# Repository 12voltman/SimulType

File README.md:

# SimulType
A collection of keyboard layouts and designs that emphasize data input through two handed use of the number pad with a keyboard or arrow keys

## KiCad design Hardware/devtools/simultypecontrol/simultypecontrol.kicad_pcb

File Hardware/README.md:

# Simultype Hardware
Described below are the different categories of PCBs and 3D files used for the creation of a SimulType keyboard.  By design, each Simultype keyboard is made up of at least 2 PCBs:  
- Key Matrix: comes in the various size standards, and contains the switches, LEDS, and some supporting ICs
- Controller Board: has the main processor, and any external connectors or peripherals (USB, battery, OLEDs, encoders, etc.)
- Space Sensor Board: flex-PCB to fit inside space bar and allow capacitive touch interaction (optional)

## Dev Tools
Currently I have a basic control board for testing that simply lets you use a Pro Micro to evaluate functionality.  Due to pin count limitations, this requires using shift registers for the column lines.  This basic control board was designed with the nice! Nano in mind (or 3rd party equivalent) and supports the extra pins needed for a battery connection.  
<br>
Additionally there is a programming tool designed to use pogo pins to mate with test points on a key matrix for testing/programming of the ICs on board such as the LED driver, identification EEPROM, and capacitive touch sensor.  This board is designed to be hand-soldered and mainly used in series production, as all its communications are carried out over I2C which is available to the standard controller.  

## Creating a controller board
Key requirements for a controller to work across the widest range of Simultype key matrixes:  
- I<sup>2</sup>C (ideally high speed) needed for secondary features and LED drivers if used
- 3.3V regulated supply (low power, needed for minor peripherals)
- Higher voltage, high-current supply (needed for LEDS, may be 5V from USB or direct battery voltage of 4.2V or whatever)
- 4 GPIO for supporting low-power mode, interrupt, and addressable LEDs
- Matrix driving
  - 24 Column drivers, ideally with moderate power sourcing support for driving hall sensors on analog boards
  - 8 Row receive lines, ideally with ADC function for analog boards
  - (Optional) To drastically reduce pin counts required, column drivers can be Serial-In Parallel-Out (SIPO) shift registers, as implemented on dev controller board

## FPC Pinout
The FPC cable linking the key matrix and the controller is designed to be standard across all variants, and if anyone else wants to use it more power to you.  Here is the pinout from 1 (leftmost) to 45 (rightmost) both when viewed from above when the keyboard is assembled.  
| Pin | Name      | Function                                                                                       |
|-----|-----------|------------------------------------------------------------------------------------------------|
| 1   | COL24     | Leftmost column drive                                                                          |
| 2   | COL23     |                                                                                                |
| 3   | COL22     |                                                                                                |
| 4   | COL21     |                                                                                                |
| 5   | COL20     |                                                                                                |
| 6   | COL19     |                                                                                                |
| 7   | COL18     |                                                                                                |
| 8   | COL17     |                                                                                                |
| 9   | COL16     |                                                                                                |
| 10  | COL15     |                                                                                                |
| 11  | COL14     |                                                                                                |
| 12  | COL13     |                                                                                                |
| 13  | COL12     |                                                                                                |
| 14  | COL11     |                                                                                                |
| 15  | COL10     |                                                                                                |
| 16  | COL9      |                                                                                                |
| 17  | ROW8      | Bottommost row receive (connect to analog input on controller if possible for analog matrix)   |
| 18  | ROW7      |                                                                                                |
| 19  | ROW6      |                                                                                                |
| 20  | ROW5      |                                                                                                |
| 21  | ROW4      |                                                                                                |
| 22  | ROW3      |                                                                                                |
| 23  | ROW2      |                                                                                                |
| 24  | ROW1      | Topmost row receive (connect to analog input on controller if possible for analog matrix)      |
| 25  | GND       |                                                                                                |
| 26  | GND       |                                                                                                |
| 27  | GND       |                                                                                                |
| 28  | 3.3V      | Supply for non-LED ICs                                                                         |
| 29  | 5V        |                                                                                                |
| 30  | 5V        | Supply for LEDS (allowed to vary, must be high power)                                          |
| 31  | 5V        |                                                                                                |
| 32  | APACLK    | Clock for APA and other clock+data LEDS (may not be used on all boards)                        |
| 33  | APANEODAT | Data for Neopixel/APA LEDs (may not be used on all boards)                                     |
| 34  | SDA       | I2C data line                                                                                  |
| 35  | SCL       | I2C clock line                                                                                 |
| 36  | INT       | Shared interrupt line, active low                                                              |
| 37  | LEDOFF    | Hard shutoff for LEDs (may be used by either LED driver, or power gating for addressable LEDs) |
| 38  | COL8      |                                                                                                |
| 39  | COL7      |                                                                                                |
| 40  | COL6      |                                                                                                |
| 41  | COL5      |                                                                                                |
| 42  | COL4      |                                                                                                |
| 43  | COL3      |                                                                                                |
| 44  | COL2      |                                                                                                |
| 45  | COL1      | Rightmost column drive                                                                         |

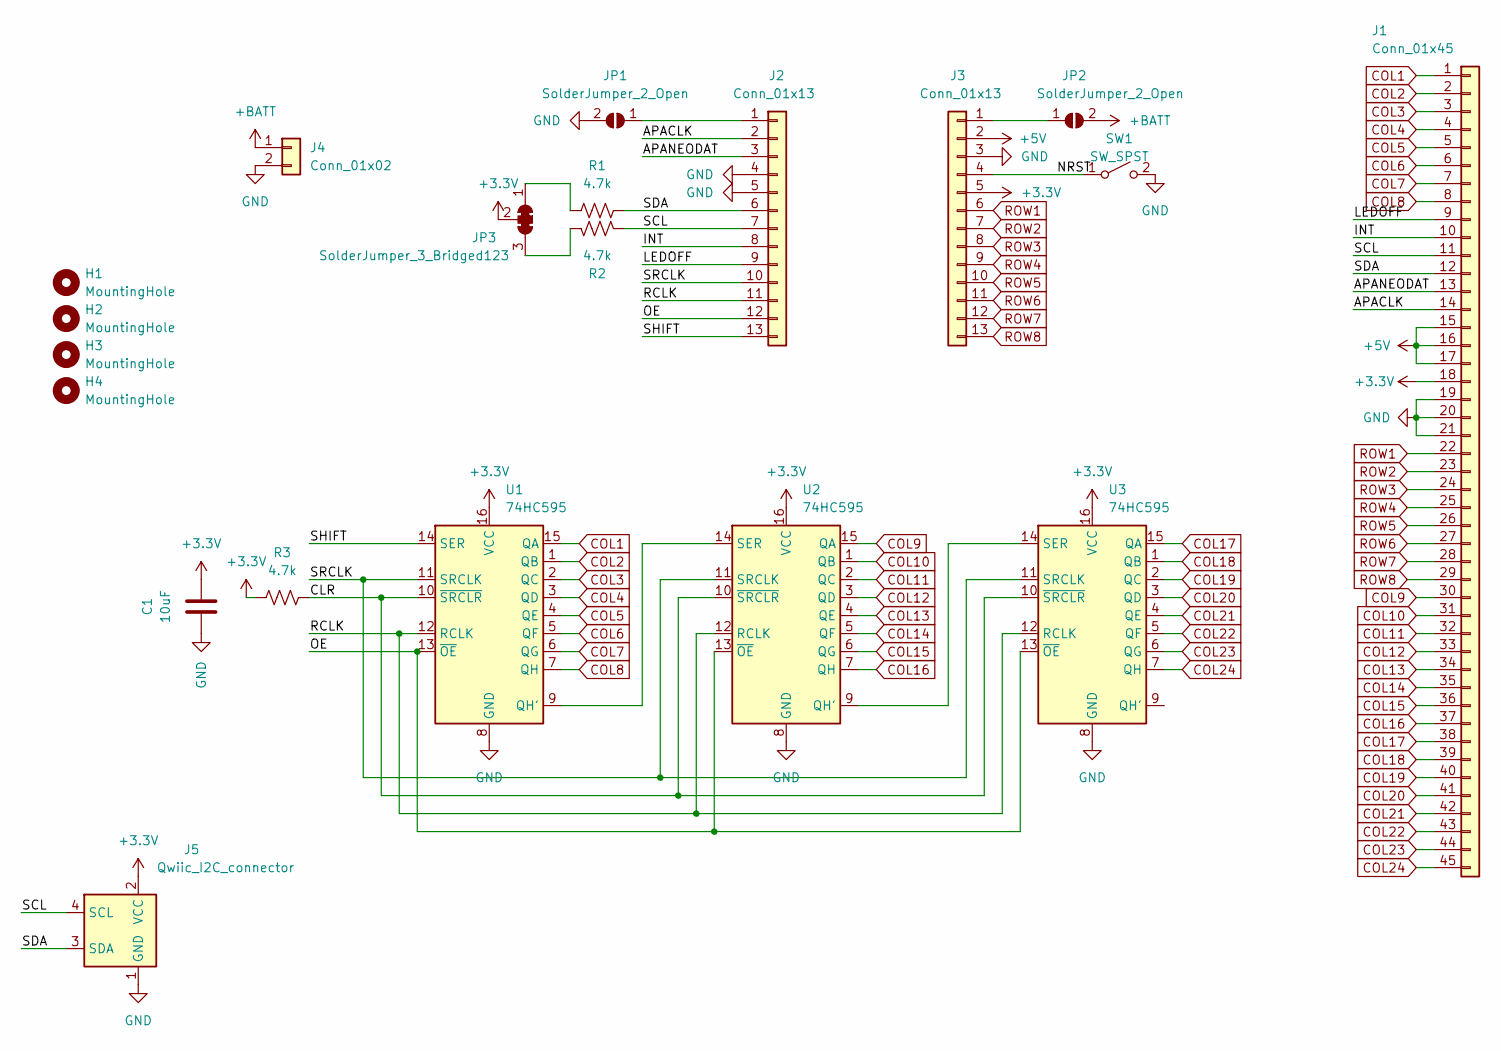
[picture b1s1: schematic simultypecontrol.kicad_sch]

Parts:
C1: 10uF; C_0805_2012Metric; LCSC C1713
H1, H2, H3, H4: MountingHole; breakoffm3hole
J1: Conn_01x45; TE_4-1734839-5_1x45-1MP_P0.5mm_Horizontal; LCSC C2998867
J2, J3: Conn_01x13; PinHeader_1x13_P2.54mm_Vertical; LCSC C2986992
J4: Conn_01x02; JST_PH_S2B-PH-K_1x02_P2.00mm_Horizontal; LCSC C49992
J5: Qwiic_I2C_connector; JST_SH_SM04B-SRSS-TB_1x04-1MP_P1.00mm_Horizontal; LCSC C7433425
JP1, JP2: SolderJumper_2_Open; SolderJumper-2_P1.3mm_Open_TrianglePad1.0x1.5mm
JP3: SolderJumper_3_Bridged123; SolderJumper-3_P1.3mm_Bridged123_RoundedPad1.0x1.5mm
R1, R2, R3: 4.7k; R_0603_1608Metric; LCSC C25999
SW1: SW_SPST; SW_PUSH_6mm; LCSC C5340136
U1, U2, U3: 74HC595; DHVQFN-16-1EP_2.5x3.5mm_P0.5mm_EP1x2mm; LCSC C730243

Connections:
+3.3V: C1.1, J1.18, J3.5, J5.2 (VCC), JP3.2 (C), R3.1, U1.16 (VCC), U2.16 (VCC), U3.16 (VCC)
+5V: J1.15, J1.16, J1.17, J3.2
+BATT: J4.1, JP2.2 (B)
/APACLK: J1.14, J2.2
/APANEODAT: J1.13, J2.3
/CLR: R3.2, U1.10 (~SRCLR), U2.10 (~SRCLR), U3.10 (~SRCLR)
/INT: J1.10, J2.8
/LEDOFF: J1.9, J2.9
/NRST: J3.4, SW1.1 (A)
/OE: J2.12, U1.13 (~OE), U2.13 (~OE), U3.13 (~OE)
/RCLK: J2.11, U1.12 (RCLK), U2.12 (RCLK), U3.12 (RCLK)
/SCL: J1.11, J2.7, J5.4 (SCL), R2.2
/SDA: J1.12, J2.6, J5.3 (SDA), R1.2
/SHIFT: J2.13, U1.14 (SER)
/SRCLK: J2.10, U1.11 (SRCLK), U2.11 (SRCLK), U3.11 (SRCLK)
COL1: J1.1, U1.15 (QA)
COL2: J1.2, U1.1 (QB)
COL3: J1.3, U1.2 (QC)
COL4: J1.4, U1.3 (QD)
COL5: J1.5, U1.4 (QE)
COL6: J1.6, U1.5 (QF)
COL7: J1.7, U1.6 (QG)
COL8: J1.8, U1.7 (QH)
COL9: J1.30, U2.15 (QA)
COL10: J1.31, U2.1 (QB)
COL11: J1.32, U2.2 (QC)
COL12: J1.33, U2.3 (QD)
COL13: J1.34, U2.4 (QE)
COL14: J1.35, U2.5 (QF)
COL15: J1.36, U2.6 (QG)
COL16: J1.37, U2.7 (QH)
COL17: J1.38, U3.15 (QA)
COL18: J1.39, U3.1 (QB)
COL19: J1.40, U3.2 (QC)
COL20: J1.41, U3.3 (QD)
COL21: J1.42, U3.4 (QE)
COL22: J1.43, U3.5 (QF)
COL23: J1.44, U3.6 (QG)
COL24: J1.45, U3.7 (QH)
GND: C1.2, J1.19, J1.20, J1.21, J2.4, J2.5, J3.3, J4.2, J5.1 (GND), J5.MP (VSS), JP1.2 (B), SW1.2 (B), U1.8 (GND), U2.8 (GND), U3.8 (GND)
unnamed: J2.1, JP1.1 (A)
unnamed: J3.1, JP2.1 (A)
unnamed: JP3.1 (A), R1.1
unnamed: JP3.3 (B), R2.1
unnamed: U1.9 (QH'), U2.14 (SER)
unnamed: U2.9 (QH'), U3.14 (SER)
ROW1: J1.22, J3.6
ROW2: J1.23, J3.7
ROW3: J1.24, J3.8
ROW4: J1.25, J3.9
ROW5: J1.26, J3.10
ROW6: J1.27, J3.11
ROW7: J1.28, J3.12
ROW8: J1.29, J3.13

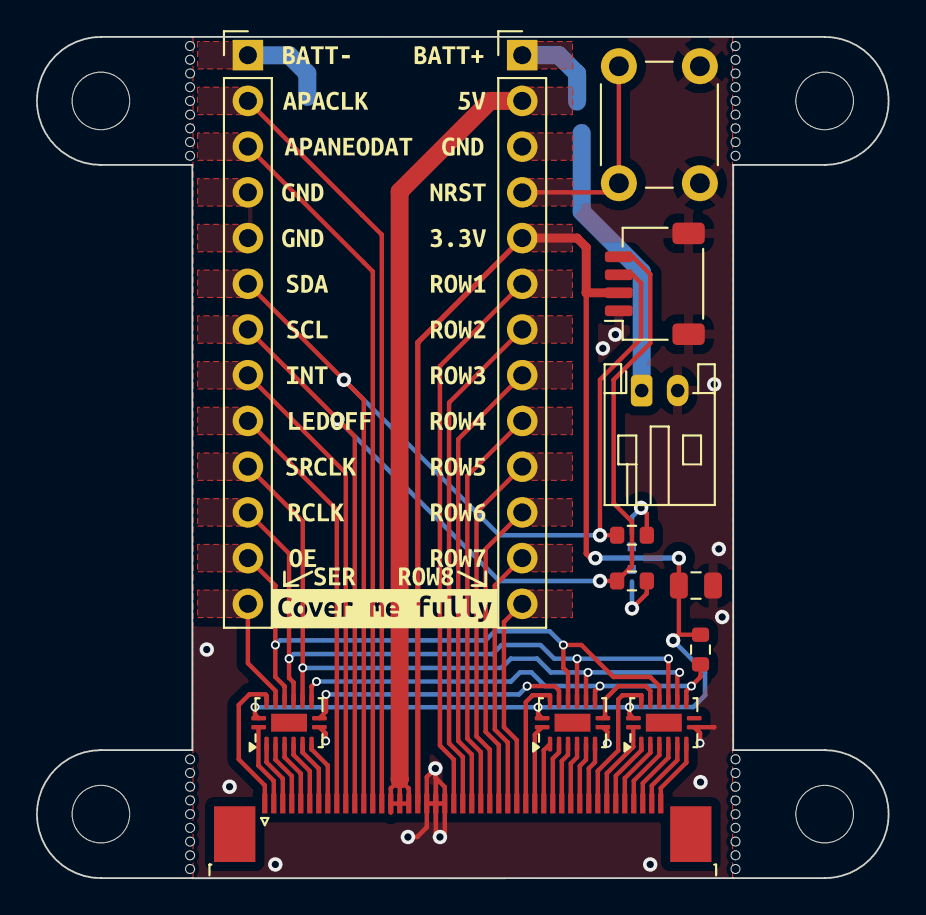
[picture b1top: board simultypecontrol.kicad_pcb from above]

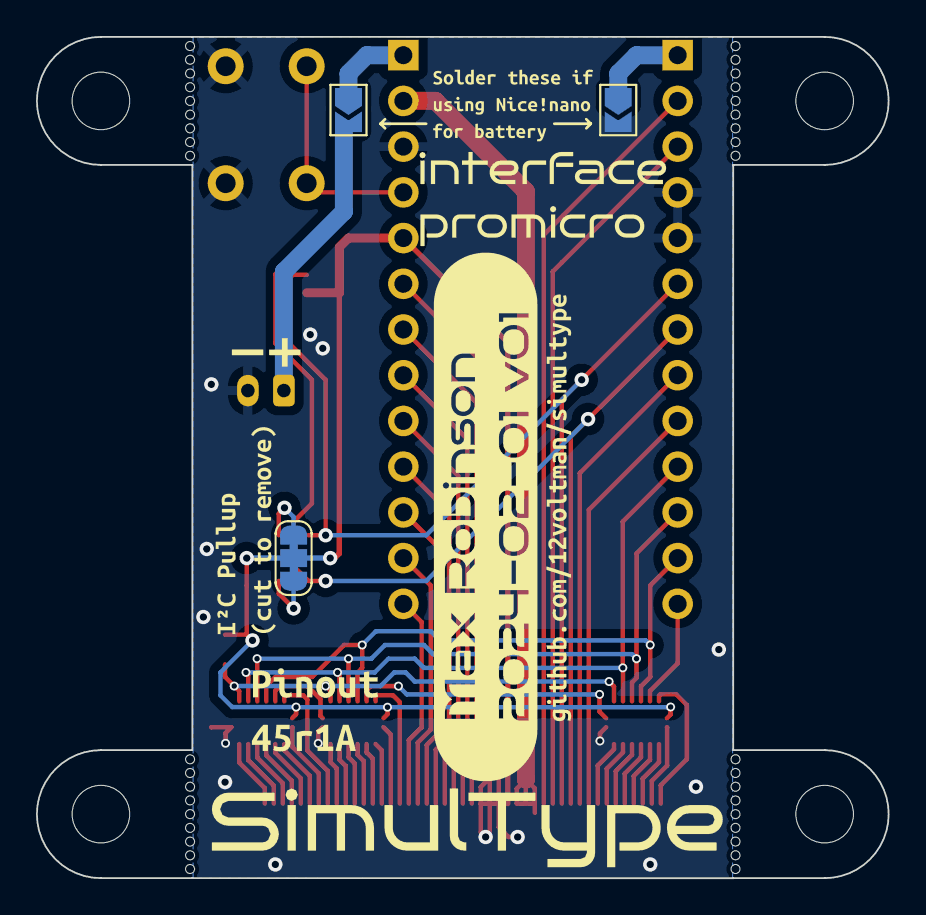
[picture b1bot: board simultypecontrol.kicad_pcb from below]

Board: 2 copper layers, 47.3 x 46.7 mm, 55 parts (11 on the bottom side), 54 nets.

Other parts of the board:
kibuzzard-65BDD6E5: G***; kibuzzard-65BDD6E5
kibuzzard-65BDD7EC: G***; kibuzzard-65BDD7EC
kibuzzard-65BDD62B: G***; kibuzzard-65BDD62B
kibuzzard-65BDD75E: G***; kibuzzard-65BDD75E
kibuzzard-65BDD614: G***; kibuzzard-65BDD614
kibuzzard-65BDD880: G***; kibuzzard-65BDD880
kibuzzard-65BE09D0: G***; kibuzzard-65BE09D0
kibuzzard-65BE0934: G***; kibuzzard-65BE0934
kibuzzard-65BEF9A5: G***; kibuzzard-65BEF9A5
kibuzzard-65BEF9C3: G***; kibuzzard-65BEF9C3
kibuzzard-65BEF9CF: G***; kibuzzard-65BEF9CF
kibuzzard-65BEF9D6: G***; kibuzzard-65BEF9D6
kibuzzard-65BEF9DC: G***; kibuzzard-65BEF9DC
kibuzzard-65BEF9E1: G***; kibuzzard-65BEF9E1
kibuzzard-65BEF9E8: G***; kibuzzard-65BEF9E8
kibuzzard-65BEF9F0: G***; kibuzzard-65BEF9F0
kibuzzard-65BEF9FD: G***; kibuzzard-65BEF9FD
kibuzzard-65BEF941: G***; kibuzzard-65BEF941
kibuzzard-65BEFA0F: G***; kibuzzard-65BEFA0F
kibuzzard-65BEFA1D: G***; kibuzzard-65BEFA1D
kibuzzard-65BEFA03: G***; kibuzzard-65BEFA03
kibuzzard-65BEFA3D: G***; kibuzzard-65BEFA3D
kibuzzard-65BEFA6D: G***; kibuzzard-65BEFA6D
kibuzzard-65BEFA08: G***; kibuzzard-65BEFA08
kibuzzard-65BEFA17: G***; kibuzzard-65BEFA17
kibuzzard-65BEFA24: G***; kibuzzard-65BEFA24
kibuzzard-65BEFA30: G***; kibuzzard-65BEFA30
kibuzzard-65BEFA36: G***; kibuzzard-65BEFA36
kibuzzard-65BEFA42: G***; kibuzzard-65BEFA42
kibuzzard-65BEFA48: G***; kibuzzard-65BEFA48
kibuzzard-65BEFA57: G***; kibuzzard-65BEFA57
kibuzzard-65BEFA60: G***; kibuzzard-65BEFA60
kibuzzard-65BEFA66: G***; kibuzzard-65BEFA66
kibuzzard-65C29BCC: G***; kibuzzard-65C29BCC
kibuzzard-65C25006: G***; kibuzzard-65C25006

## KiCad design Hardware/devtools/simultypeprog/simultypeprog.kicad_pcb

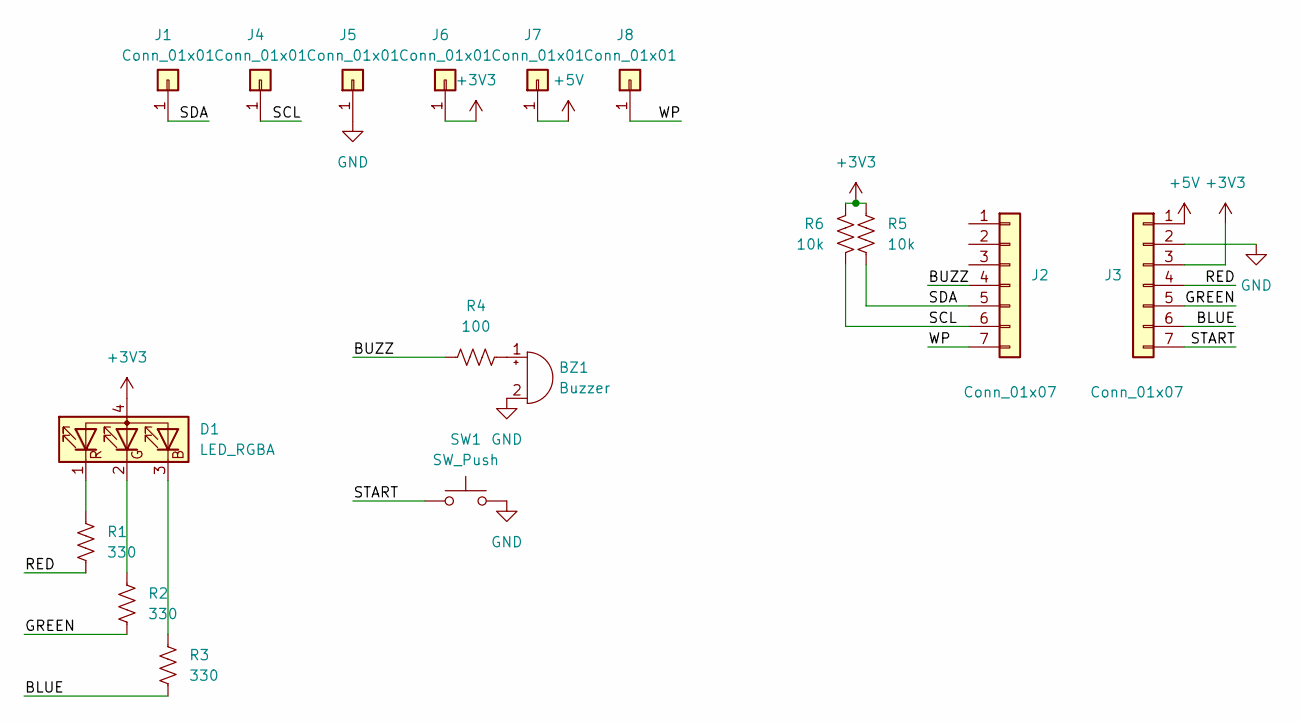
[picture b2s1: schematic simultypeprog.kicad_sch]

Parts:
BZ1: Buzzer; Buzzer_TDK_PS1240P02BT_D12.2mm_H6.5mm
D1: LED_RGBA; LED_D5.0mm-4_RGB
J1, J4, J5, J6, J7, J8: Conn_01x01; SolderWirePad_1x01_SMD_1x2mm
J2, J3: Conn_01x07; PinHeader_1x07_P2.54mm_Vertical
R1, R2, R3: 330; R_Axial_DIN0207_L6.3mm_D2.5mm_P7.62mm_Horizontal
R4: 100; R_Axial_DIN0207_L6.3mm_D2.5mm_P7.62mm_Horizontal
R5, R6: 10k; R_Axial_DIN0207_L6.3mm_D2.5mm_P7.62mm_Horizontal
SW1: SW_Push; SW_PUSH-12mm

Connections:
+3V3: D1.4 (A), J3.3, J6.1, R5.2, R6.2
+5V: J3.1, J7.1
/BLUE: J3.6, R3.2
/BUZZ: J2.4, R4.1
/GREEN: J3.5, R2.2
/RED: J3.4, R1.2
/SCL: J2.6, J4.1, R6.1
/SDA: J1.1, J2.5, R5.1
/START: J3.7, SW1.1
/WP: J2.7, J8.1
GND: BZ1.2 (-), J3.2, J5.1, SW1.2
unnamed: BZ1.1 (+), R4.2
unnamed: D1.3 (BK), R3.1
unnamed: D1.2 (GK), R2.1
unnamed: D1.1 (RK), R1.1

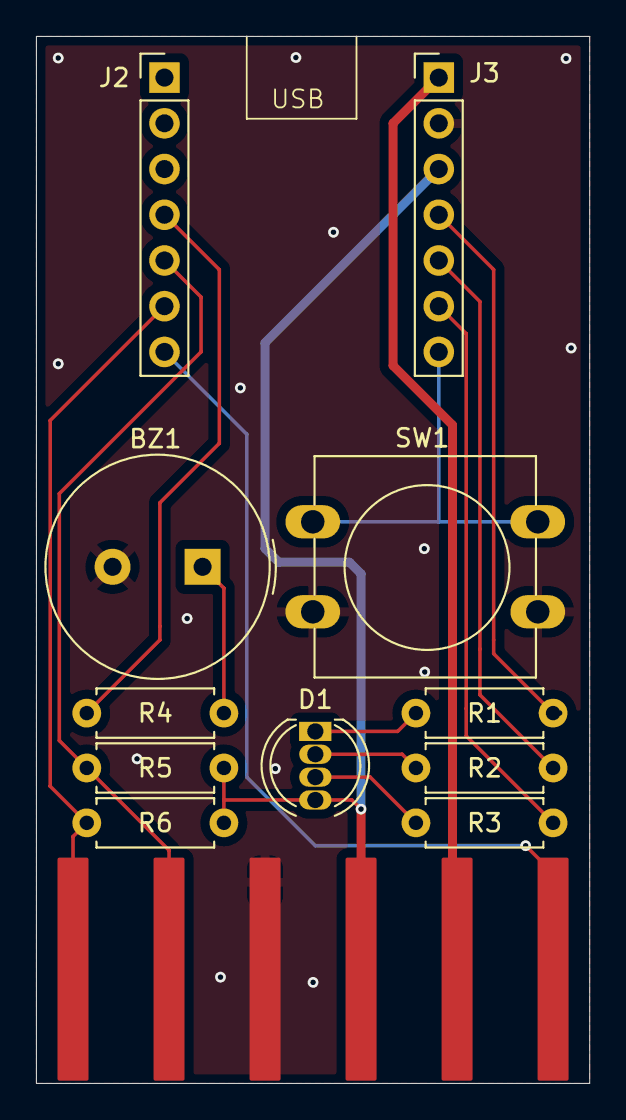
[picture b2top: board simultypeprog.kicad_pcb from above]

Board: 2 copper layers, 30.7 x 58.2 mm, 17 parts (0 on the bottom side), 15 nets.

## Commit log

2021-08-26 Basic version layout import
2021-08-26 Big version layout import
2021-08-26 General outline of parts for standard version
2021-08-26 General outline of parts for larger version
2021-08-29 Found some parts
2021-08-29 Update SimulTypeStandard
2023-09-27 Create SimulTypeMEGAbig
2023-09-27 Create SimulTypeMEGAsmall
2024-02-02 Create SimulTypeUltrasmall
    A stupidly large layout that maxes out LEDs and column lines
2024-02-02 Create SimulTypeUltrabig
    Big escape key version of ultra
2024-07-02 Moving files
2024-07-02 Added PCB files from PC
    Forgot I never uploaded these. Whoops.
2024-07-02 Added layout options infographic
2024-07-02 Organization rework
2024-07-02 Minor graphics cleanup
2024-07-02 Added 3d models
2024-07-02 Updated 3d models
